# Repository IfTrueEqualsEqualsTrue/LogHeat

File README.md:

# Temperature Logger

This project is a temperature logging system developed during the 2024 Biomedical Engineering Master Class at Grenoble INP. The system is designed to record temperature data in real-time, offering students practical experience in data acquisition, processing, and visualization, relevant to biomedical applications.

## Features
- **Real-time temperature logging**: Captures temperature data from a connected sensor.
- **Data storage**: Saves logged data for later analysis.
- **Data visualization**: Provides a graphical interface for displaying temperature trends over time.
- **Simple UI**: User-friendly interface for ease of use by non-technical users.
  
This app does not include the possibility for the MCP inputs but it can be easily tweaked in the file ```SpiInteface.py```

## Hardware Requirements
- Thermocouple sensor
- MAX31855 thermocouple conditionning circuit

## Running the Application

The main.py file is the entry point for the application. The required packages can be installed in a new virtual environment using:

```bash
pip install -r requirements.txt
```

To run the application, execute the main file using the following command:

```bash
python src/main.py
```

## Compiling

To use the app on as a standalone, it can be compiled using pyinstaller.

Use the following command to compile the app:

```bash
pyinstaller main.spec
```

This will create a dist folder containing the compiled app. Compile on the os the app should be used on, but keep in mind spidev works only on the raspberry pi.

## Contributors
Grenoble INP Biomedical Engineering Students:
- Guillaume Boulet
- Paul Ménard
- Lucie Martinal
- Guillermo Lazarin

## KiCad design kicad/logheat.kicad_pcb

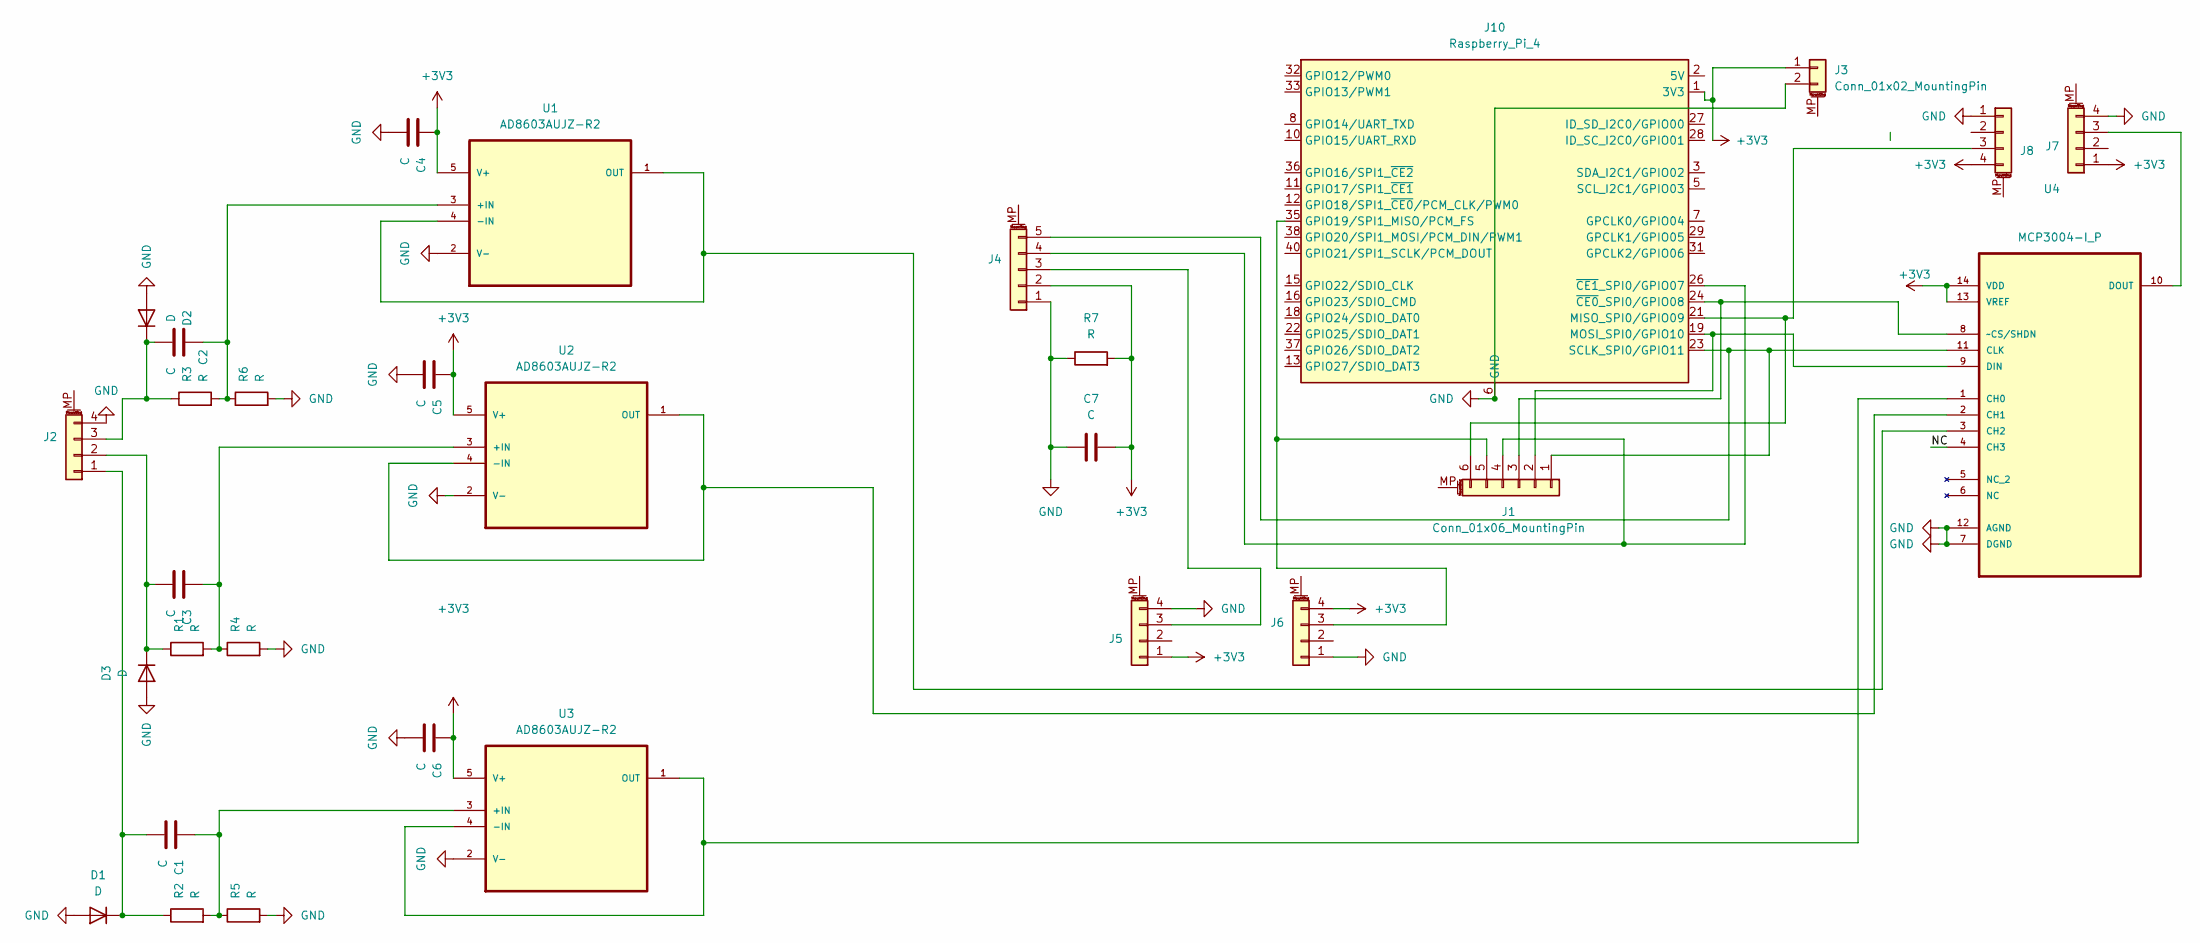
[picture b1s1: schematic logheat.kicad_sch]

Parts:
C1, C2, C3, C4, C5, C6, C7: C; C_Disc_D3.0mm_W1.6mm_P2.50mm
D1, D2, D3: D; R_Axial_DIN0204_L3.6mm_D1.6mm_P7.62mm_Horizontal
J1: Conn_01x06_MountingPin; PinSocket_1x06_P2.54mm_Vertical
J2: Analog_inputs; TerminalBlock_MaiXu_MX126-5.0-04P_1x04_P5.00mm
J3: Conn_01x02_MountingPin; PinHeader_1x02_P2.54mm_Vertical
J4: Circuit_conditiono; PinHeader_1x05_P2.54mm_Vertical
J5, J6: protec_condit; PinHeader_1x04_P2.54mm_Vertical
J7, J8: protec_mcp; PinHeader_1x04_P2.54mm_Vertical
J10: Raspberry_Pi_4; PinHeader_2x20_P2.54mm_Vertical
R1, R2, R3, R4, R5, R6, R7: R; R_Axial_DIN0204_L3.6mm_D1.6mm_P7.62mm_Horizontal
U1, U2, U3: AD8603AUJZ-R2; AD3603; MPN AD8603AUJZ-R2
U4: MCP3004-I_P; MCP3004 ISL; MPN MCP3004-I/P

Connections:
+3V3: C4.1, C5.1, C6.1, C7.1, J3.1, J4.2, J5.1, J6.4, J7.1, J8.4, J10.1 (3V3), J10.17 (3V3), R7.2, U1.5 (V+), U2.5 (V+), U3.5 (V+), U4.13 (VREF), U4.14 (VDD)
/NC: U4.4 (CH3)
GND: C4.2, C5.2, C6.2, C7.2, D1.2 (A), D2.2 (A), D3.2 (A), J2.4, J3.2, J4.1, J5.4, J6.1, J7.4, J8.1, J10.6 (GND), J10.9 (GND), J10.14 (GND), J10.20 (GND), J10.25 (GND), J10.30 (GND), J10.34 (GND), J10.39 (GND), R4.2, R5.2, R6.2, R7.1, U1.2 (V-), U2.2 (V-), U3.2 (V-), U4.7 (DGND), U4.12 (AGND)
unnamed: C1.2, D1.1 (K), J2.1, R2.1
unnamed: C2.2, D2.1 (K), J2.3, R3.1
unnamed: C3.2, D3.1 (K), J2.2, R1.1
unnamed: J1.1, J4.5, J10.23 (SCLK_SPI0/GPIO11), U4.11 (CLK)
unnamed: J1.2, J10.19 (MOSI_SPI0/GPIO10), U4.9 (DIN)
unnamed: J1.3, J10.24 (~CE0_SPI0/GPIO08), U4.8 (~CS/SHDN)
unnamed: J1.4, J4.4, J10.26 (~CE1_SPI0/GPIO07)
unnamed: J1.5, J6.3, J10.35 (GPIO19/SPI1_MISO/PCM_FS)
unnamed: J1.6, J8.3, J10.21 (MISO_SPI0/GPIO09)
unnamed: J4.3, J5.3
unnamed: J7.3, U4.10 (DOUT)
unnamed: J10.2 (5V), J10.4 (5V)
unnamed: C2.1, R3.2, R6.1, U1.3 (+IN)
unnamed: U1.1 (OUT), U1.4 (-IN), U4.3 (CH2)
unnamed: C3.1, R1.2, R4.1, U2.3 (+IN)
unnamed: U2.1 (OUT), U2.4 (-IN), U4.2 (CH1)
unnamed: C1.1, R2.2, R5.1, U3.3 (+IN)
unnamed: U3.1 (OUT), U3.4 (-IN), U4.1 (CH0)

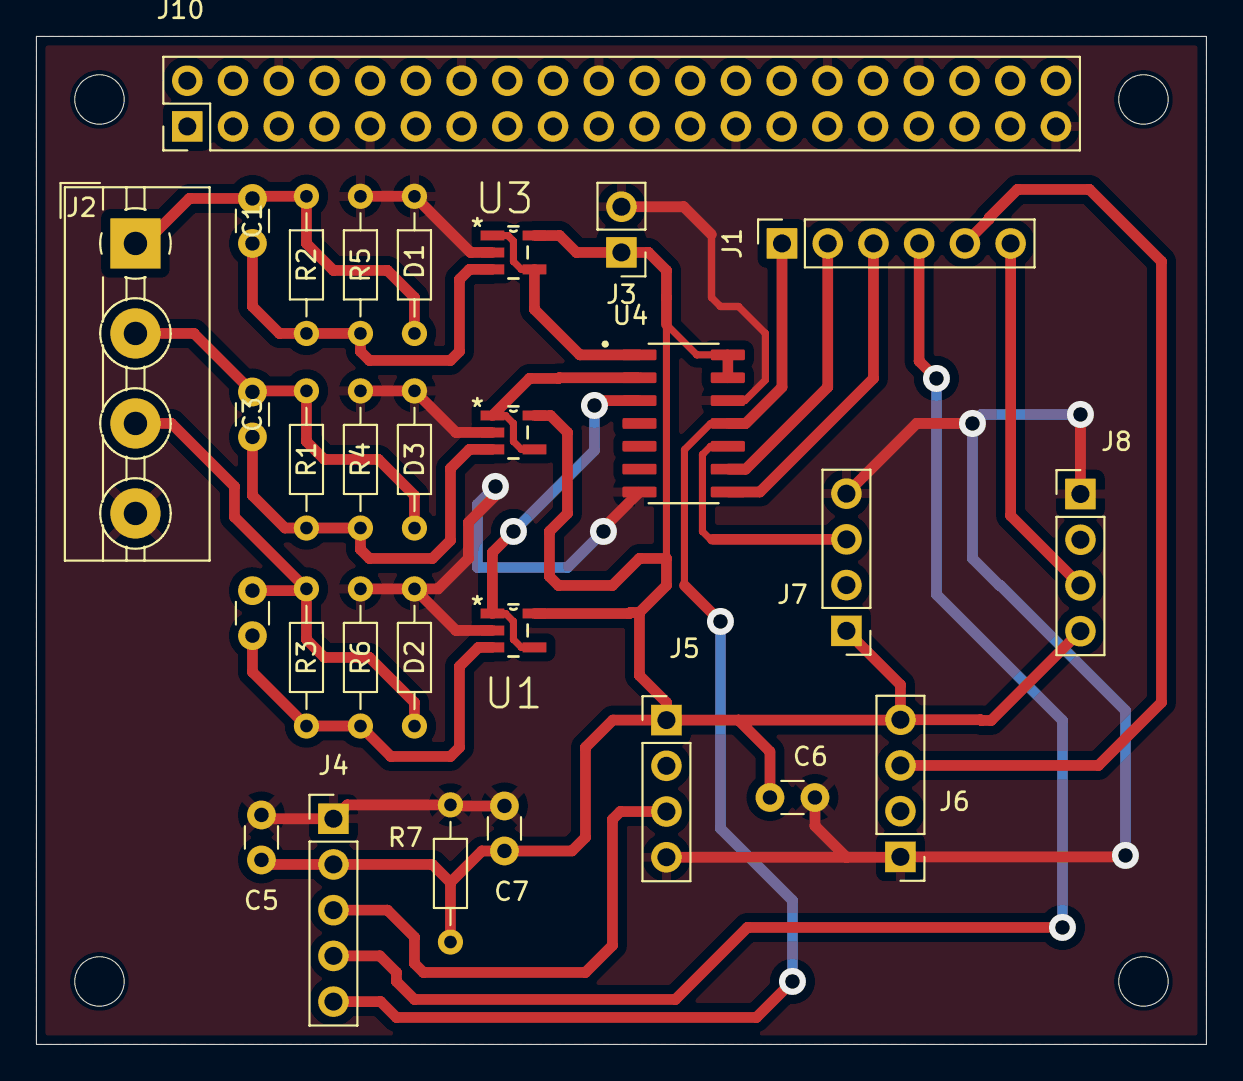
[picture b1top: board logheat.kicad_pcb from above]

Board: 2 copper layers, 65.0 x 56.0 mm, 29 parts (0 on the bottom side), 20 nets.

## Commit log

2024-10-02 adding arduino script
2024-10-02 Update arduino_script.ino voltage
2024-10-09 Create Try
2024-10-09 Testing tools for virtual ports
2024-10-09 cleaned emulator functions
2024-10-09 refactored repository
2024-10-09 single-instanced the simulator and reader
2024-10-09 tools for user interface
2024-10-09 Real-time value plotting from com port
2024-10-09 adding requirements file
2024-10-09 some visuals
2024-10-16 thermocouple writer and reader using MAX31855
2024-10-16 used readline on serial to handle data; adapted emulator
2024-10-16 testing app for linux compilation
2024-10-23 changed com port and y-scale
2024-10-23 first try on interface
2024-10-23 created csv facilities and bound it to the reader
2024-10-23 fixed conflict between TkAgg and ctk by local import
2024-10-23 vertical lines, start /stop
2024-10-23 csv manager cleaning
2024-10-23 Cleaned LiveValuesPlotting.py and reworked all the animation structure
2024-10-23 stop_saving no longer blocks the mainloop
2024-10-23 switching com ports is now effective
2024-10-23 fixed redundant data in csv
2024-10-23 added path utilities for compiling
2024-10-23 compilation files
2024-10-23 OptionMenu now offers real com ports options
2024-10-23 placeholder for compilation
2024-11-13 initial commit of the WebApp.py
2024-11-13 added com port list and toggle button on the webapp interface
2024-11-13 bound the toggle button and com port selector to the backend
2024-11-13 refactored and tried a plotly graph integration
2024-11-13 first working version
2024-11-13 moved js and css to static
2024-11-13 add the vertical line on save toggle
2024-11-13 refactored some files
2024-11-20 updated requirements
2024-11-20 updated arduino output frequency
2024-11-20 implemented mean on measure values to improve precision
2024-11-20 biggered font size and axes padding
2024-11-20 reworked the interface
2024-11-20 light logo, autoscale temperature and visual improvements
2024-11-20 applied calibration function
2024-11-27 first attempt to fix bitmap loading on raspberry
2024-11-27 added tkinter finder in hidden imports
2024-11-27 removed window icon not supported on linux
2024-11-27 fix conflicts between serial and pyserial
2024-11-27 added pyserial to hidden imports
2024-11-27 debug serial read method
2024-11-27 fixed nan received from serail raising value error
2024-12-18 added test file for rpi hat
2024-12-18 fixed spi bus
2024-12-18 debug spi statement
2024-12-18 correct spi device
2024-12-18 Create versiongpt
2024-12-18 try gpt version
2025-01-14 changed trame analysis
2025-01-14 last straw
2025-01-20 changed input from COM to SPI
2025-01-20 removed com ports interface and autostart spi
2025-01-20 changed import statement
2025-01-20 de-commented spidev import
2025-01-21 removed temp csv
2025-01-21 reduced window size and induced offset
2025-01-21 adapted size window
2025-01-21 increased labelpad
2025-01-21 changed window size
2025-01-22 Commented, refactored, updated readme and requirements
2025-01-22 added kicad project
2025-04-02 added emulation tools commented some code
